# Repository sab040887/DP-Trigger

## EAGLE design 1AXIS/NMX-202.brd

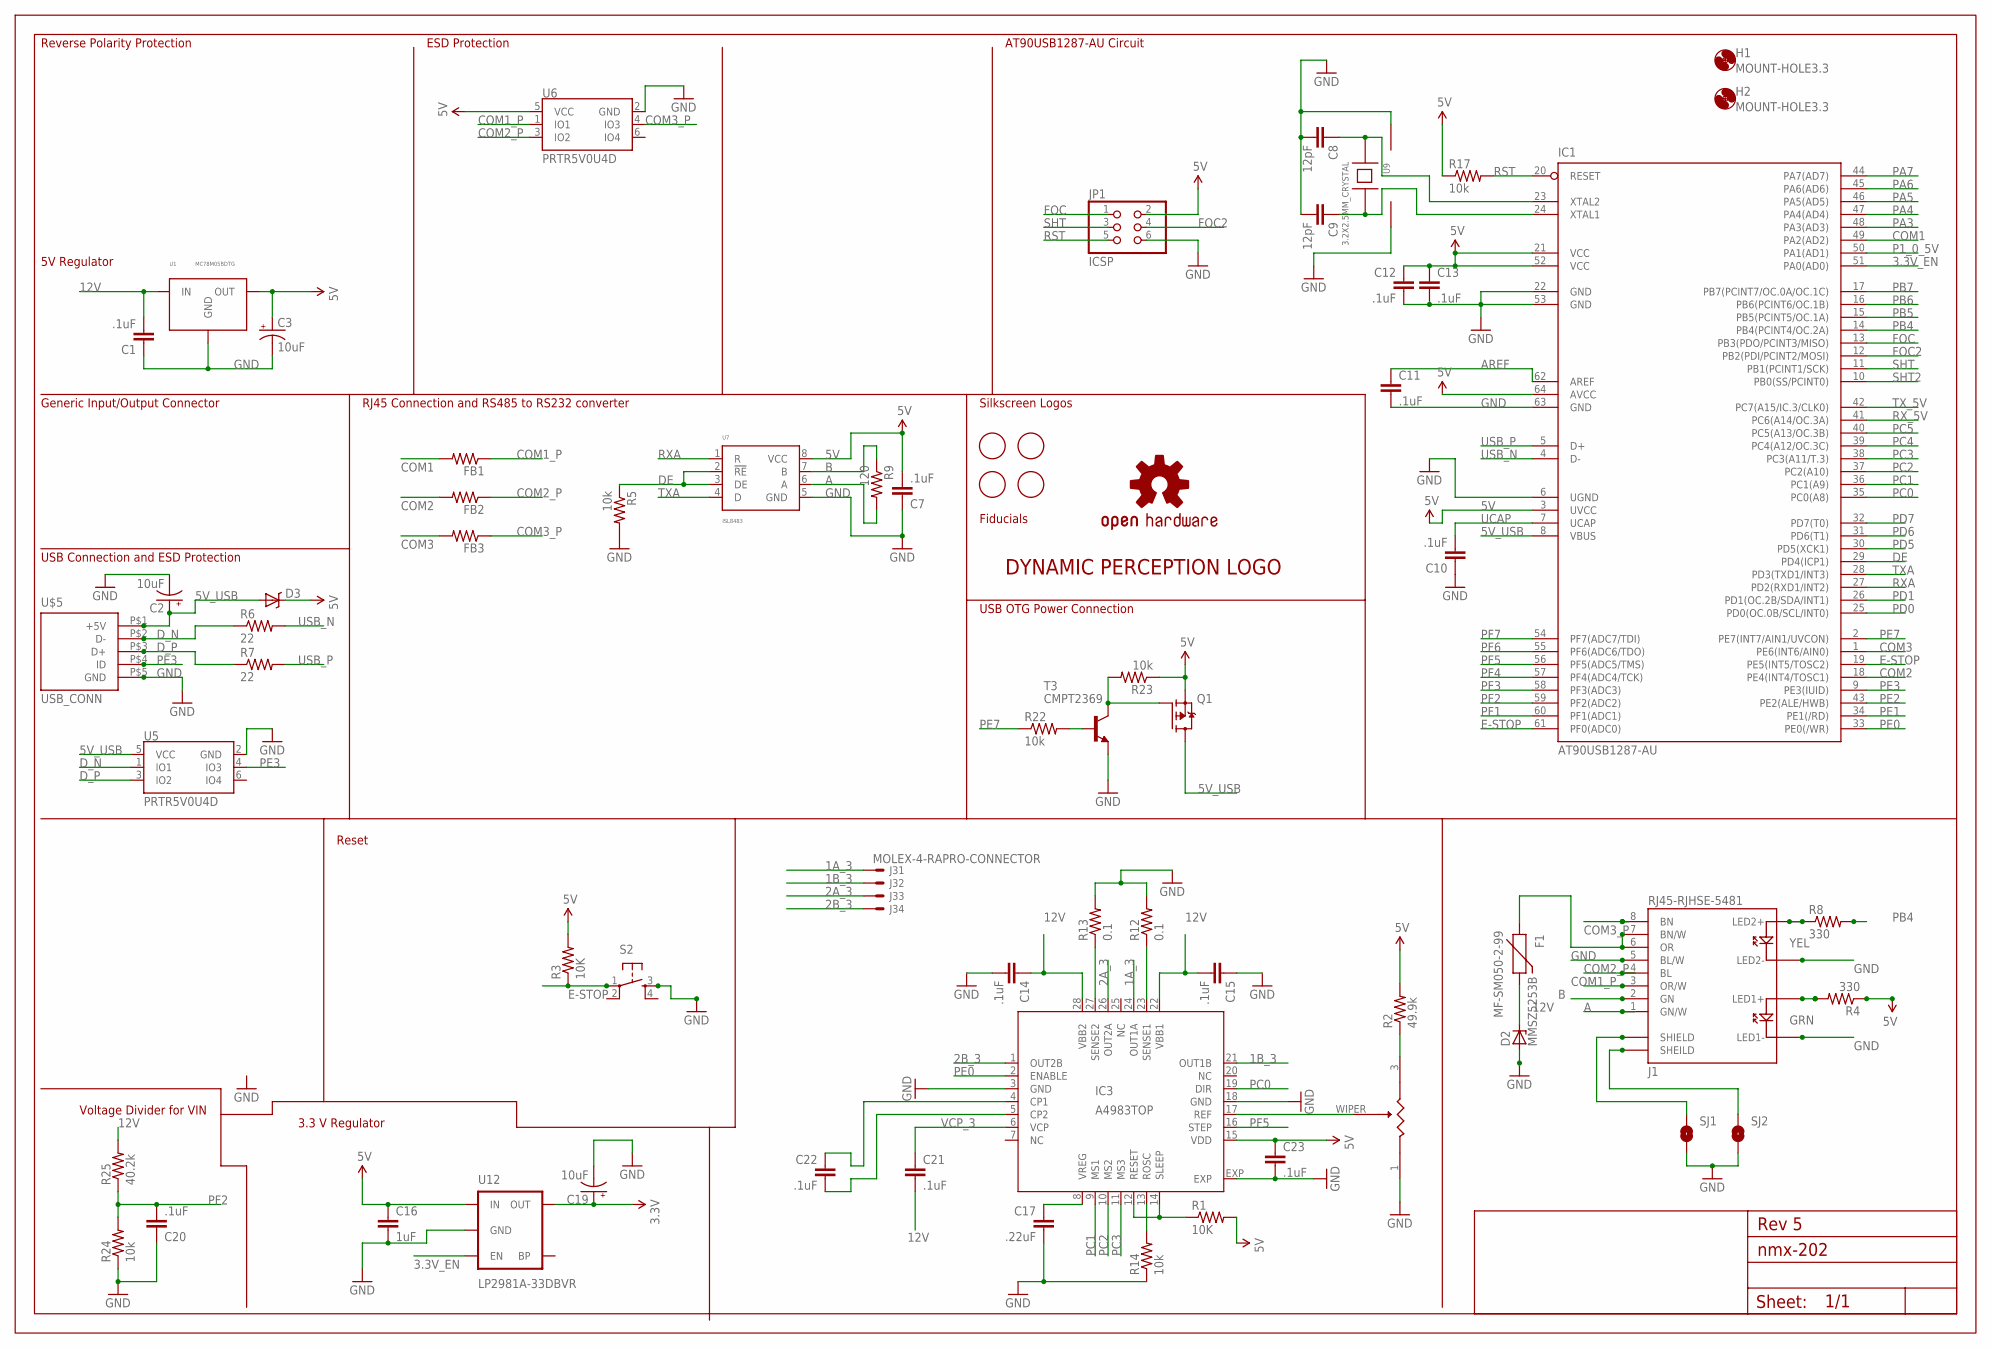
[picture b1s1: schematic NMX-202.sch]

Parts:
C1, C7, C10, C11, C12, C13, C14, C15, C20, C21, C22, C23: .1uF; 0402-CAP; MPN TMK105BJ104KV-F
C2, C3, C19: 10uF; EIA3216; MPN T491A106M016AT
C8, C9: 12pF; 0402-CAP; MPN C1005C0G1H120J050BA
C16: 1uF; 0402-CAP; MPN C1005X5R1C105K050BC
C17: .22uF; 0402-CAP; MPN TMK105BJ224KVHF
D2: MMSZ5253B; SOD123; MPN MMSZ5253B
D3: DIODE-SCHOTTKY-BAT20J; SOD-323; MPN PMEG3010BEA,115
F1: MF-SM050-2-99; PTC-2920; MPN 0ZCD0050FF2C
FB1, FB2, FB3: HZ0402B102R-10; R0402; MPN HZ0402B102R-10
FRAME2: A3L-LOCSILK_SCREEN; DRAWING_NAME
H1, H2: MOUNT-HOLE3.3; 3,3
IC1: AT90USB1287-AU; TQFP64; MPN AT90USB1287-AU
IC3: A4983TOP; QFN28ET; MPN A4983SETTR-T
J1: RJ45-RJHSE-5481; RJ45-RJHSE
J3: MOLEX-4-RAPRO-CONNECTOR; PRO_CONNECTOR; MPN 0022053041
JP1: ICSP; 2X03; MPN 67996-406HLF
Q1: P-CHANNEL_MOSFET; SOT23-3; MPN FDV304P
R1, R3: 10K; R0402_BOTTOM; MPN RC0402FR-0710KL
R2: 49.9k; R0402_BOTTOM; MPN RC0402FR-0749K9L
R4, R8: 330; R0402; MPN RC0402FR-07330RL
R5, R17, R22, R23, R24: 10k; R0402; MPN RC0402FR-0710KL
R6, R7: 22; R0402; MPN RC0402JR-0722RL
R9: 120; R0402; MPN RC0402JR-07120RL
R12, R13: 0.1; R0603; MPN RU1608FR100CS
R14: 10k; R0402_BOTTOM; MPN RC0402FR-0720KL
R25: 40.2k; R0402; MPN RC0402FR-0740K2L
S2: TAC_SWITCH; TACTICLE_SWITCH_SMD_EVQP0_BOT; MPN EVQ-P0Q02Q
SJ1, SJ2: SJ_1WAY; SJ_2
T3: CMPT2369; SOT23-BEC; MPN BC847BMTF
U1: MC78M05BDTG; DPAK-3; MPN MC78M05BDTRKG
U5, U6: PRTR5V0U4D; SOT23-6; MPN PRTR5V0U4D
U7: ISL8483; SO-08; MPN SN65176BD
U9: 3.2X2.5MM_CRYSTAL; 3.2X2.5MM; MPN CX3225SB16000E0FPZ25
U11: CADJ; 3MM_SMD; MPN TC33X-2-103E
U12: LP2981A-33DBVR; SOT23-5; MPN LP2981A-33DBVR
U$1: DP_LOGOMICRO; DP_LOGO_MICRO
U$2: OSHW-LOGOS; OSHW-LOGO-S
U$3, U$4, U$6, U$7: FIDUCIAL; FIDUCIAL_1MM
U$5: USB_CONN; 10118194-0001LF

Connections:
1A_3: IC3.24 (OUT1A), J3.P$1
1B_3: IC3.21 (OUT1B), J3.P$2
2A_3: IC3.26 (OUT2A), J3.P$3
2B_3: IC3.1 (OUT2B), J3.P$4
3.3V: C19.A (+), U12.5 (OUT)
3.3V_EN: IC1.51 (PA0(AD0)), U12.3 (EN)
5V: C3.A (+), C7.2, C12.1, C13.1, C16.1, C23.1, D3.C, IC1.3 (UVCC), IC1.21 (VCC), IC1.52 (VCC), IC1.64 (AVCC), IC3.15 (VDD), JP1.2, Q1.S, R1.2, R2.2, R3.2, R4.1, R17.1, R23.1, U1.2 (OUT), U6.5 (VCC), U7.8 (VCC), U12.1 (IN)
5V_USB: C2.A (+), D3.A, IC1.8 (VBUS), Q1.D, U5.5 (VCC), U$5.P$1 (+5V)
12V: C1.2, C14.1, C15.2, C21.2, D2.C, F1.P$2 (2), IC3.22 (VBB1), IC3.28 (VBB2), R25.2, U1.1 (IN)
A: J1.1 (GN/W), R9.2, U7.6 (A)
AREF: C11.1, IC1.62 (AREF)
ARST3: IC3.12 (RESET), IC3.14 (SLEEP), R1.1
B: J1.2 (GN), R9.1, U7.7 (B)
COM1: FB1.2, IC1.49 (PA2(AD2))
COM1_P: FB1.1, J1.3 (OR/W), U6.1 (IO1)
COM2: FB2.2, IC1.18 (PE4(INT4/TOSC1))
COM2_P: FB2.1, J1.4 (BL), U6.3 (IO2)
COM3: FB3.2, IC1.1 (PE6(INT6/AIN0))
COM3_P: FB3.1, J1.8 (BN), U6.4 (IO3)
DE: IC1.29 (PD4(ICP1)), R5.1, U7.2 (!RE), U7.3 (DE)
D_N: R6.1, U5.1 (IO1), U$5.P$2 (D-)
D_P: R7.1, U5.3 (IO2), U$5.P$3 (D+)
E-STOP: IC1.19 (PE5(INT5/TOSC2)), IC1.61 (PF0(ADC0)), R3.1, S2.1
FOC: IC1.13 (PB3(PDO/PCINT3/MISO)), JP1.1
FOC2: IC1.12 (PB2(PDI/PCINT2/MOSI)), JP1.4
GND: C1.1, C2.C (-), C3.C (-), C7.1, C8.2, C9.2, C10.1, C11.2, C12.2, C13.2, C14.2, C15.1, C16.2, C17.2, C19.C (-), C20.1, C23.2, D2.A, IC1.6 (UGND), IC1.22 (GND), IC1.53 (GND), IC1.63 (GND), IC3.3 (GND), IC3.18 (GND), IC3.EXP, J1.5 (BL/W), J1.LE1D- (LED1-), J1.LED2-, JP1.6, R5.2, R12.2, R13.2, R14.1, R24.1, S2.3, SJ1.2, SJ2.2, T3.E, U1.4 (GND), U5.2 (GND), U6.2 (GND), U7.5 (GND), U9.2 (GND), U9.4, U11.1, U12.2 (GND), U$5.P$5 (GND)
unnamed: F1.P$1 (1), J1.6 (OR), J1.7 (BN/W)
unnamed: R22.2, T3.B
unnamed: C22.2, IC3.5 (CP2)
unnamed: IC3.17 (REF), U11.WIPER (2)
unnamed: C22.1, IC3.4 (CP1)
unnamed: J1.LED1+, R4.2
unnamed: IC3.23 (SENSE1), R12.1
unnamed: IC3.27 (SENSE2), R13.1
unnamed: J1.SHIELD@0 (SHIELD), SJ1.1
unnamed: J1.SHEILD@1 (SHEILD), SJ2.1
unnamed: Q1.G, R23.2, T3.C
unnamed: J1.LED2+, R8.1
unnamed: R2.1, U11.3
P1_0_5V: IC1.50 (PA1(AD1))
PA3: IC1.48 (PA3(AD3))
PA4: IC1.47 (PA4(AD4))
PA5: IC1.46 (PA5(AD5))
PA6: IC1.45 (PA6(AD6))
PA7: IC1.44 (PA7(AD7))
PB4: IC1.14 (PB4(PCINT4/OC.2A)), R8.2
PB5: IC1.15 (PB5(PCINT5/OC.1A))
PB6: IC1.16 (PB6(PCINT6/OC.1B))
PB7: IC1.17 (PB7(PCINT7/OC.0A/OC.1C))
PC0: IC1.35 (PC0(A8)), IC3.19 (DIR)
PC1: IC1.36 (PC1(A9)), IC3.9 (MS1)
PC2: IC1.37 (PC2(A10)), IC3.10 (MS2)
PC3: IC1.38 (PC3(A11/T.3)), IC3.11 (MS3)
PC4: IC1.39 (PC4(A12/OC.3C))
PC5: IC1.40 (PC5(A13/OC.3B))
PD0: IC1.25 (PD0(OC.0B/SCL/INT0))
PD1: IC1.26 (PD1(OC.2B/SDA/INT1))
PD5: IC1.30 (PD5(XCK1))
PD6: IC1.31 (PD6(T1))
PD7: IC1.32 (PD7(T0))
PE0: IC1.33 (PE0(/WR)), IC3.2 (ENABLE)
PE1: IC1.34 (PE1(/RD))
PE2: IC1.43 (PE2(ALE/HWB))
PE3: IC1.9 (PE3(IUID)), U5.4 (IO3), U$5.P$4 (ID)
PE7: IC1.2 (PE7(INT7/AIN1/UVCON)), R22.1
PF1: IC1.60 (PF1(ADC1))
PF2: C20.2, IC1.59 (PF2(ADC2)), R24.2, R25.1
PF3: IC1.58 (PF3(ADC3))
PF4: IC1.57 (PF4(ADC4/TCK))
PF5: IC1.56 (PF5(ADC5/TMS)), IC3.16 (STEP)
PF6: IC1.55 (PF6(ADC6/TDO))
PF7: IC1.54 (PF7(ADC7/TDI))
ROSC3: IC3.13 (ROSC), R14.2
RST: IC1.20 (RESET), JP1.5, R17.2
RXA: IC1.27 (PD2(RXD1/INT2)), U7.1 (R)
RX_5V: IC1.41 (PC6(A14/OC.3A))
SHT: IC1.11 (PB1(PCINT1/SCK)), JP1.3
SHT2: IC1.10 (PB0(SS/PCINT0))
TXA: IC1.28 (PD3(TXD1/INT3)), U7.4 (D)
TX_5V: IC1.42 (PC7(A15/IC.3/CLK0))
UCAP: C10.2, IC1.7 (UCAP)
USB_N: IC1.4 (D-), R6.2
USB_P: IC1.5 (D+), R7.2
VCP_3: C21.1, IC3.6 (VCP)
VREG3: C17.1, IC3.8 (VREG)
XTAL1: C9.1, IC1.24 (XTAL1), U9.3
XTAL2: C8.1, IC1.23 (XTAL2), U9.1

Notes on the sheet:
3.3 V Regulator
Reverse Polarity Protection
5V Regulator
Generic Input/Output Connector
USB Connection and ESD Protection
RJ45 Connection and RS485 to RS232 converter
ESD Protection
AT90USB1287-AU Circuit
Voltage Divider for VIN
USB OTG Power Connection
Silkscreen Logos
Fiducials
Rev 5
Reset

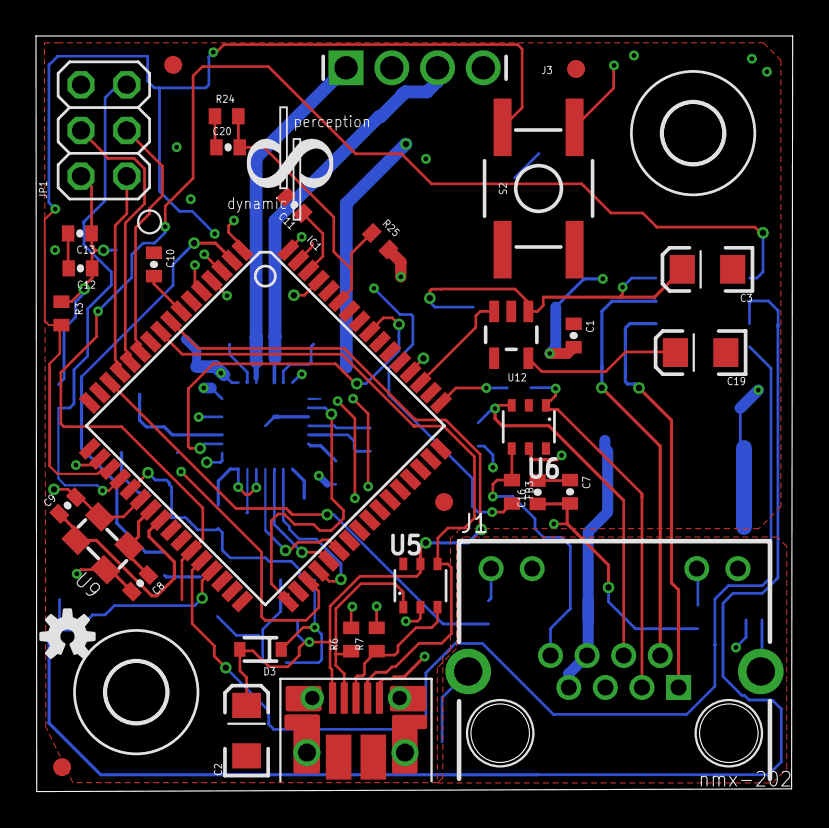
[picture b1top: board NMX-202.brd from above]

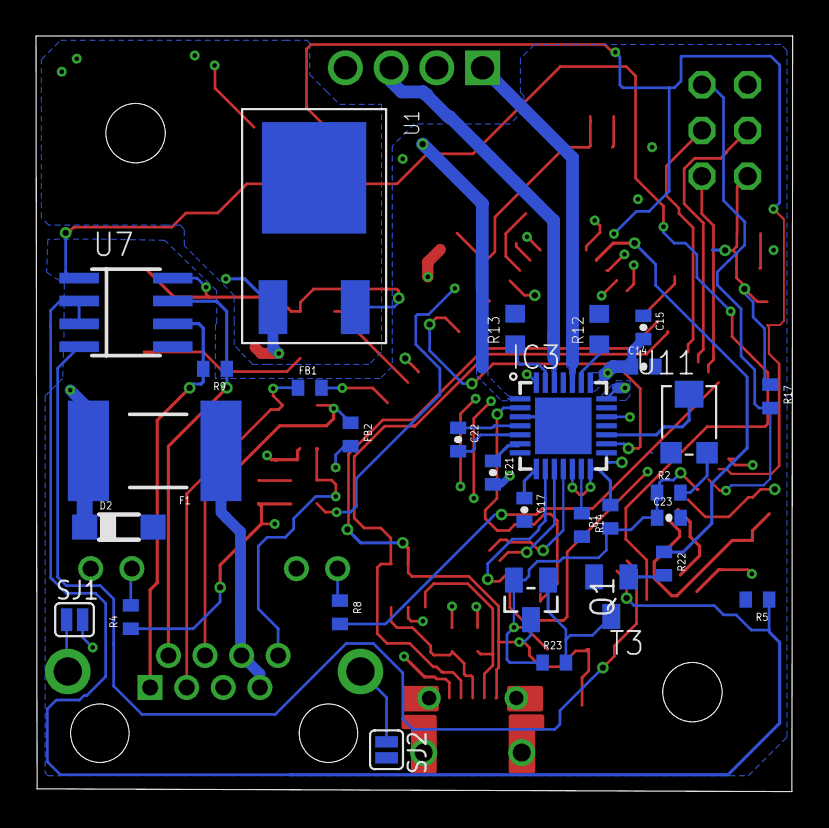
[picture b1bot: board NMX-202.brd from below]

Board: 4 copper layers, 42.0 x 42.0 mm, 69 parts (29 on the bottom side), 61 nets.

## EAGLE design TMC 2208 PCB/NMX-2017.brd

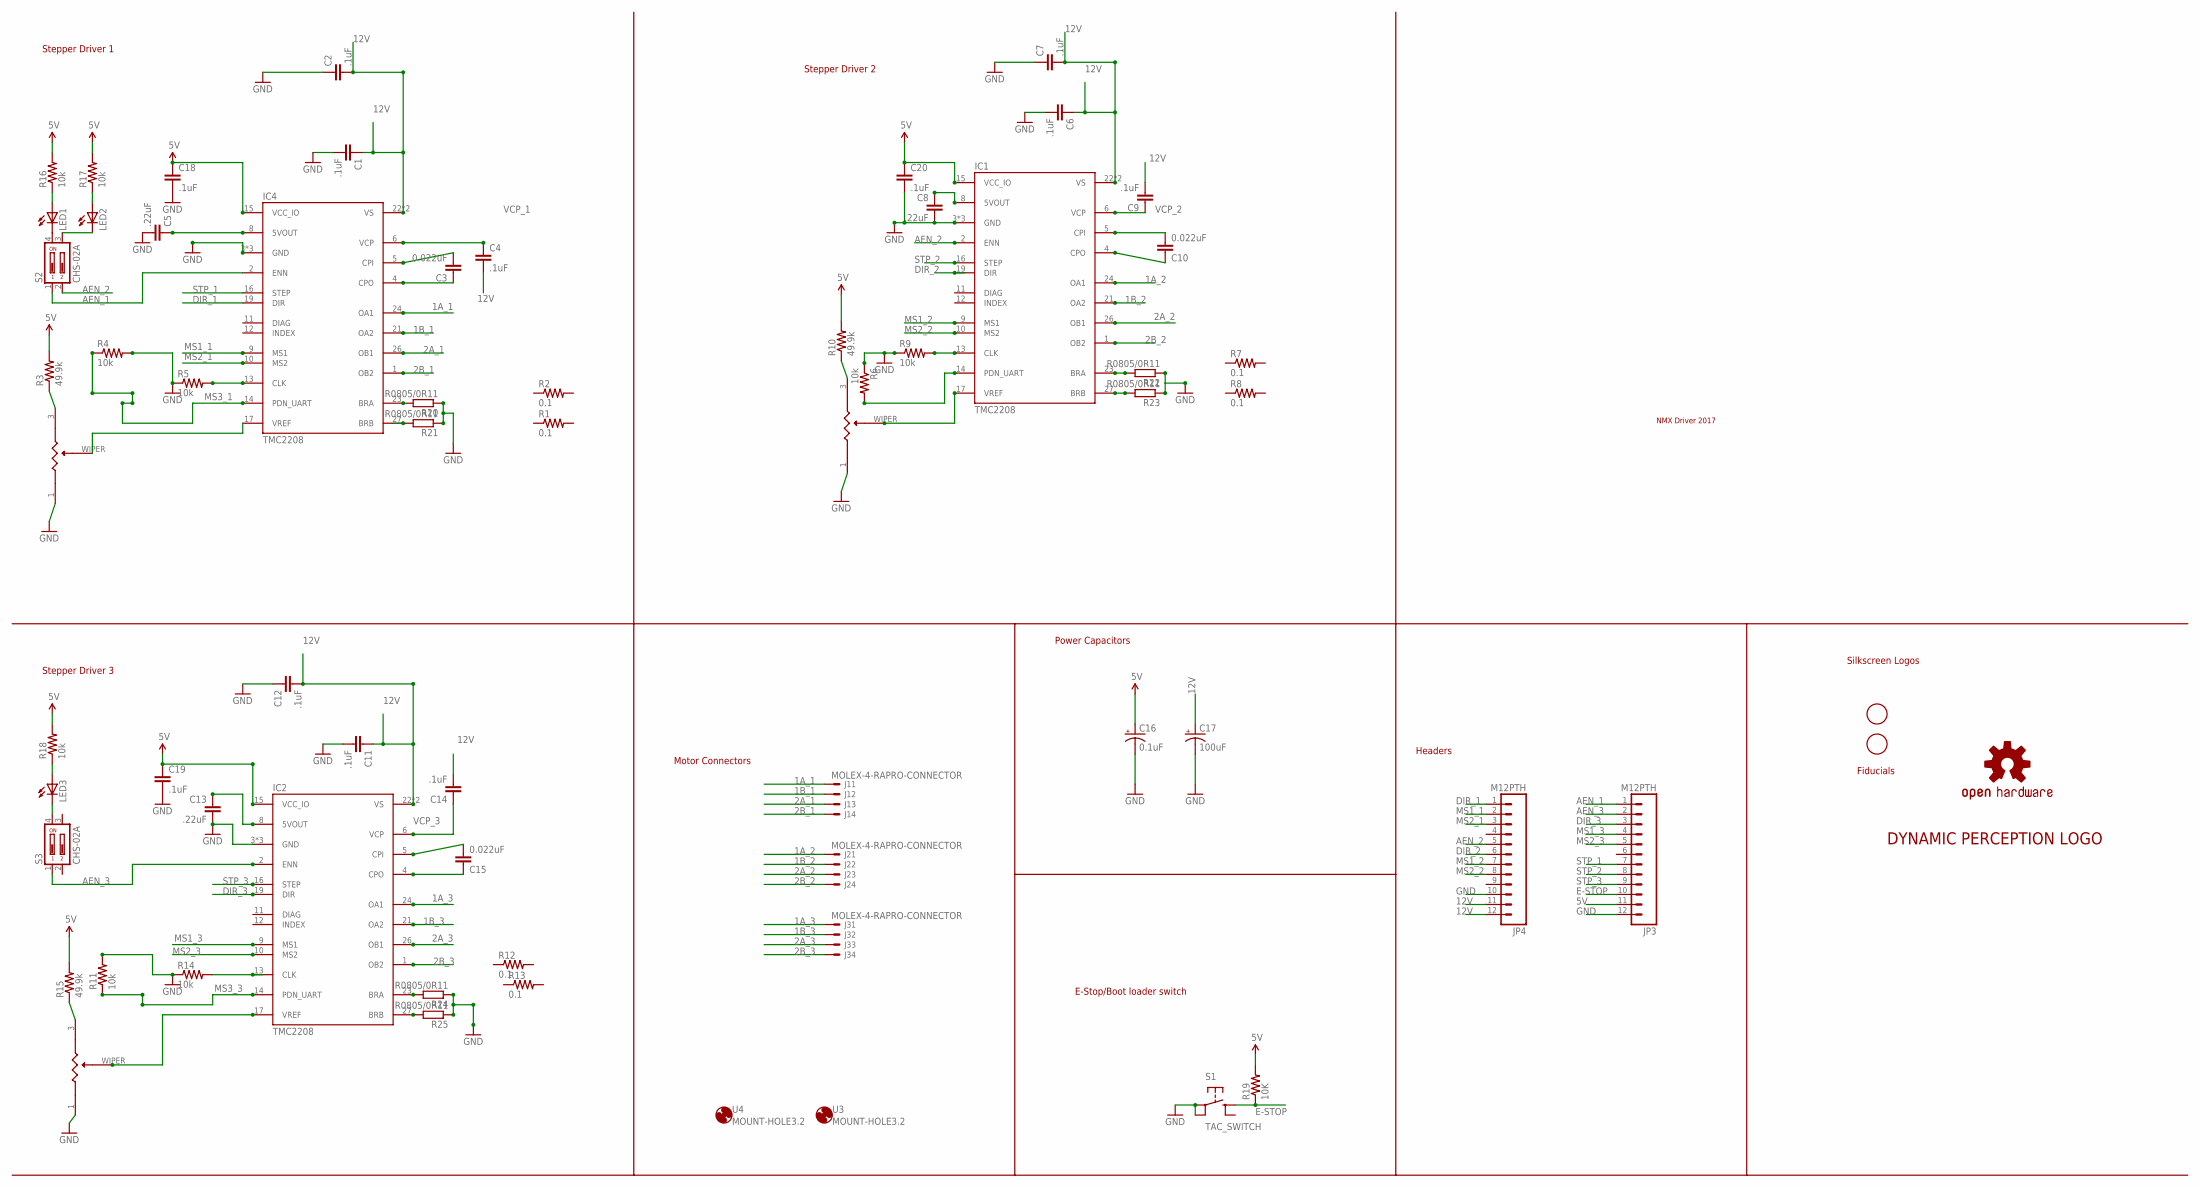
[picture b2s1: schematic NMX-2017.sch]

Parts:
C1, C2, C4, C6, C7, C9, C11, C12, C14, C18, C19, C20: .1uF; 0402-CAP; MPN TMK105BJ104KV-F
C3, C10, C15: 0.022uF; 0402-CAP; MPN TMK105BJ104KV-F
C5, C8, C13: .22uF; 0402-CAP; MPN TMK105BJ224KVHF
C16: 0.1uF; EIA3216; MPN T491A106M016AT
C17: 100uF; PANASONIC_D; MPN EEE-1EA101XP
IC1, IC2, IC4: TMC2208; QFN28-PAD
J1, J2, J3: MOLEX-4-RAPRO-CONNECTOR; PRO_CONNECTOR; MPN 0022053041
JP3, JP4: M12PTH; 1X12; MPN 0901200132
LED1, LED2, LED3: LED0603; LED-0603; MPN LB Q39G-L2N2-35-1
R1, R2, R7, R8, R12, R13: 0.1; R0603; MPN RU1608FR100CS
R3, R10, R15: 49.9k; R0402_BOTTOM; MPN RC0402FR-0749K9L
R4, R5, R6, R9, R11, R14: 10k; R0402_BOTTOM; MPN RC0402FR-0720KL
R16, R17, R18: 10k; R0402_BOTTOM; MPN RC0402FR-0714KL
R19: 10K; R0402_BOTTOM; MPN RC0402FR-0710KL
R20, R21, R22, R23, R24, R25: R0805/0R11; M0805
S1: TAC_SWITCH; TAC_SWITCH_THR; MPN 2-1825027-0
S2, S3: CHS-02A
U1, U2, U5: CADJ; 3MM_SMD; MPN TC33X-2-103E
U3, U4: MOUNT-HOLE3.2; 3,2
U$1: DP_LOGOMICRO; DP_LOGO_MICRO
U$2: OSHW-LOGOS; OSHW-LOGO-S
U$3, U$4: FIDUCIAL; FIDUCIAL_1MM

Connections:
1A_1: IC4.24 (OA1), J1.P$1
1A_2: IC1.24 (OA1), J2.P$1
1A_3: IC2.24 (OA1), J3.P$1
1B_1: IC4.21 (OA2), J1.P$2
1B_2: IC1.21 (OA2), J2.P$2
1B_3: IC2.21 (OA2), J3.P$2
2A_1: IC4.26 (OB1), J1.P$3
2A_2: IC1.26 (OB1), J2.P$3
2A_3: IC2.26 (OB1), J3.P$3
2B_1: IC4.1 (OB2), J1.P$4
2B_2: IC1.1 (OB2), J2.P$4
2B_3: IC2.1 (OB2), J3.P$4
5V: C16.A (+), C18.1, C19.1, C20.1, IC1.15 (VCC_IO), IC2.15 (VCC_IO), IC4.15 (VCC_IO), JP3.11, R3.2, R10.2, R15.2, R16.2, R17.2, R18.2, R19.2
12V: C1.1, C2.2, C4.2, C6.1, C7.2, C9.2, C11.1, C12.2, C14.2, C17.+, IC1.22 (VS), IC1.28 (VS), IC2.22 (VS), IC2.28 (VS), IC4.22 (VS), IC4.28 (VS), JP4.11, JP4.12
AEN_1: IC4.2 (ENN), JP3.1, S2.1
AEN_2: IC1.2 (ENN), JP4.5, S2.2
AEN_3: IC2.2 (ENN), JP3.2, S3.1
DIR_1: IC4.19 (DIR), JP4.1
DIR_2: IC1.19 (DIR), JP4.6
DIR_3: IC2.19 (DIR), JP3.3
E-STOP: JP3.10, R19.1, S1.B (3)
GND: C1.2, C2.1, C5.2, C6.2, C7.1, C8.2, C11.2, C12.1, C13.2, C16.C (-), C17.-, C18.2, C19.2, C20.2, IC1.3 (GND), IC1.18 (GND), IC1.TP (GND), IC2.3 (GND), IC2.18 (GND), IC2.TP (GND), IC4.3 (GND), IC4.18 (GND), IC4.TP (GND), JP3.12, JP4.10, R4.2, R5.1, R6.1, R9.1, R11.2, R14.1, R20.1, R21.1, R22.1, R23.1, R24.1, R25.1, S1.A (1), S1.P$1 (2), U1.1, U2.1, U5.1
MS1_1: IC4.9 (MS1), JP4.2
MS1_2: IC1.9 (MS1), JP4.7
MS1_3: IC2.9 (MS1), JP3.4
MS2_1: IC4.10 (MS2), JP4.3
MS2_2: IC1.10 (MS2), JP4.8
MS2_3: IC2.10 (MS2), JP3.5
MS3_1: IC4.14 (PDN_UART), R4.1
MS3_2: IC1.14 (PDN_UART), R6.2
MS3_3: IC2.14 (PDN_UART), R11.1
unnamed: C10.1, IC1.4 (CPO)
unnamed: C10.2, IC1.5 (CPI)
unnamed: IC1.17 (VREF), U2.WIPER (2)
unnamed: R10.1, U2.3
unnamed: C15.1, IC2.4 (CPO)
unnamed: C15.2, IC2.5 (CPI)
unnamed: IC2.23 (BRA), R24.2
unnamed: IC2.17 (VREF), U5.WIPER (2)
unnamed: R15.1, U5.3
unnamed: LED1.A, R16.1
unnamed: LED2.A, R17.1
unnamed: LED3.A, R18.1
unnamed: LED1.C, S2.4
unnamed: LED2.C, S2.3
unnamed: LED3.C, S3.4
unnamed: IC2.27 (BRB), R25.2
unnamed: C3.1, IC4.4 (CPO)
unnamed: C3.2, IC4.5 (CPI)
unnamed: IC1.23 (BRA), R22.2
unnamed: IC4.27 (BRB), R21.2
unnamed: IC4.17 (VREF), U1.WIPER (2)
unnamed: R3.1, U1.3
unnamed: IC4.23 (BRA), R20.2
unnamed: IC1.27 (BRB), R23.2
ROSC1: IC4.13 (CLK), R5.2
ROSC2: IC1.13 (CLK), R9.2
ROSC3: IC2.13 (CLK), R14.2
STP_1: IC4.16 (STEP), JP3.7
STP_2: IC1.16 (STEP), JP3.8
STP_3: IC2.16 (STEP), JP3.9
VCP_1: C4.1, IC4.6 (VCP)
VCP_2: C9.1, IC1.6 (VCP)
VCP_3: C14.1, IC2.6 (VCP)
VREG1: C5.1, IC4.8 (5VOUT)
VREG2: C8.1, IC1.8 (5VOUT)
VREG3: C13.1, IC2.8 (5VOUT)

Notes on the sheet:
Stepper Driver 1
Stepper Driver 2
Stepper Driver 3
Motor Connectors
E-Stop/Boot loader switch
Headers
Power Capacitors
Silkscreen Logos
Fiducials
NMX Driver 2017

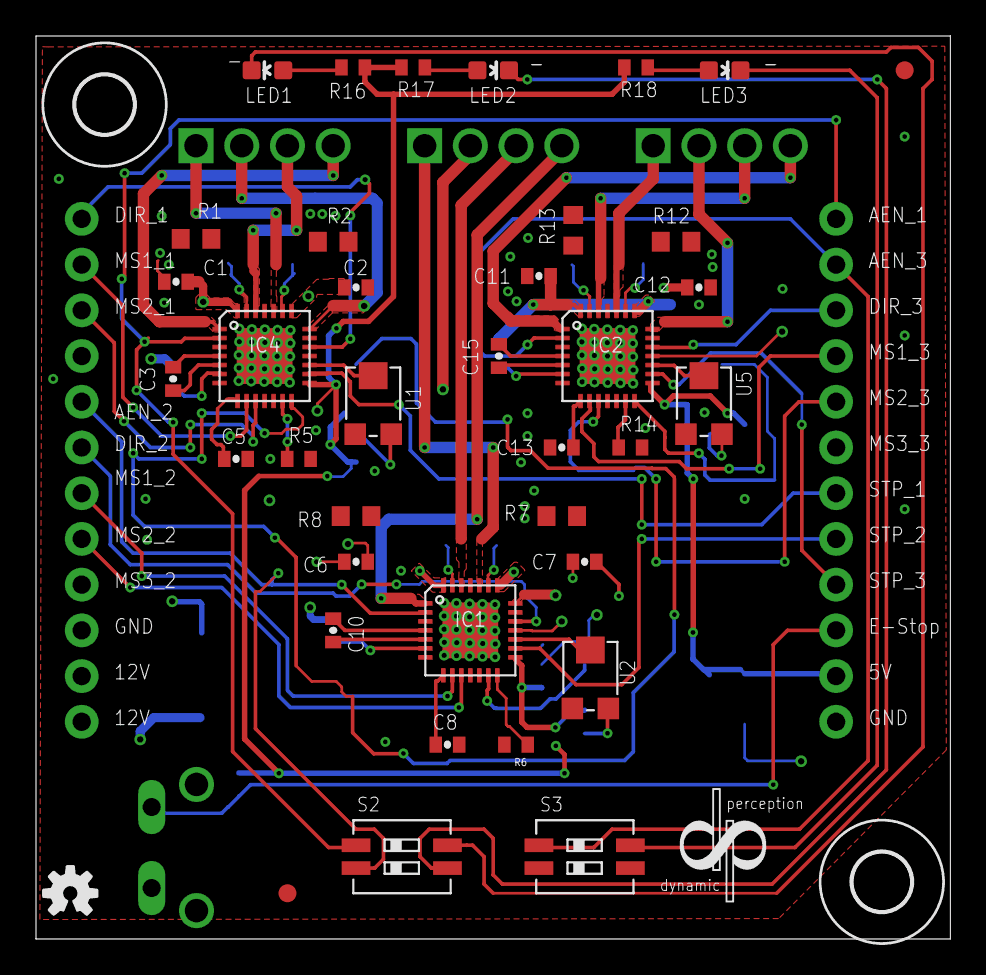
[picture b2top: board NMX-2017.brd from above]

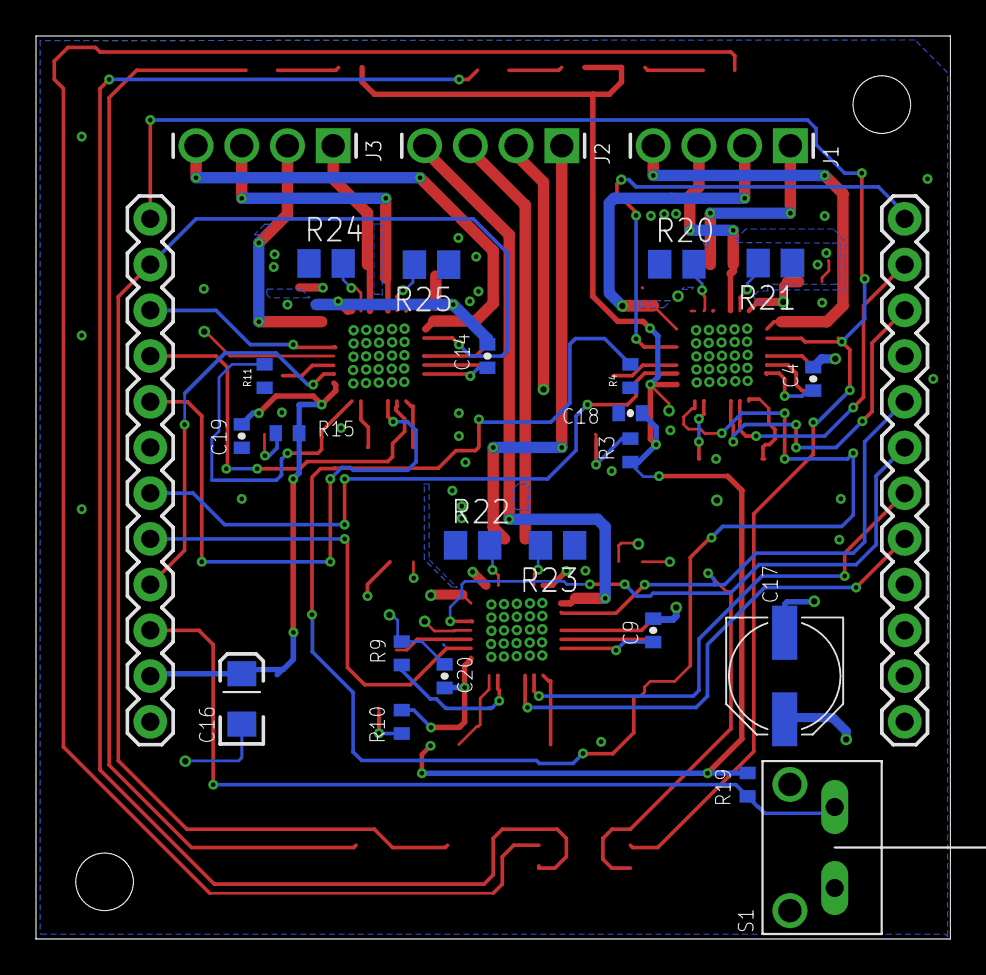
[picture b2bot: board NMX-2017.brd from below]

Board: 4 copper layers, 50.8 x 50.2 mm, 68 parts (26 on the bottom side), 67 nets.

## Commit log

2018-03-07 Add All Files

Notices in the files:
parts and their libraries:
SparkFun-Capacitors: Licensing: Creative Commons ShareAlike 4.0 International - https://creativecommons.org/licenses/by-sa/4.0
